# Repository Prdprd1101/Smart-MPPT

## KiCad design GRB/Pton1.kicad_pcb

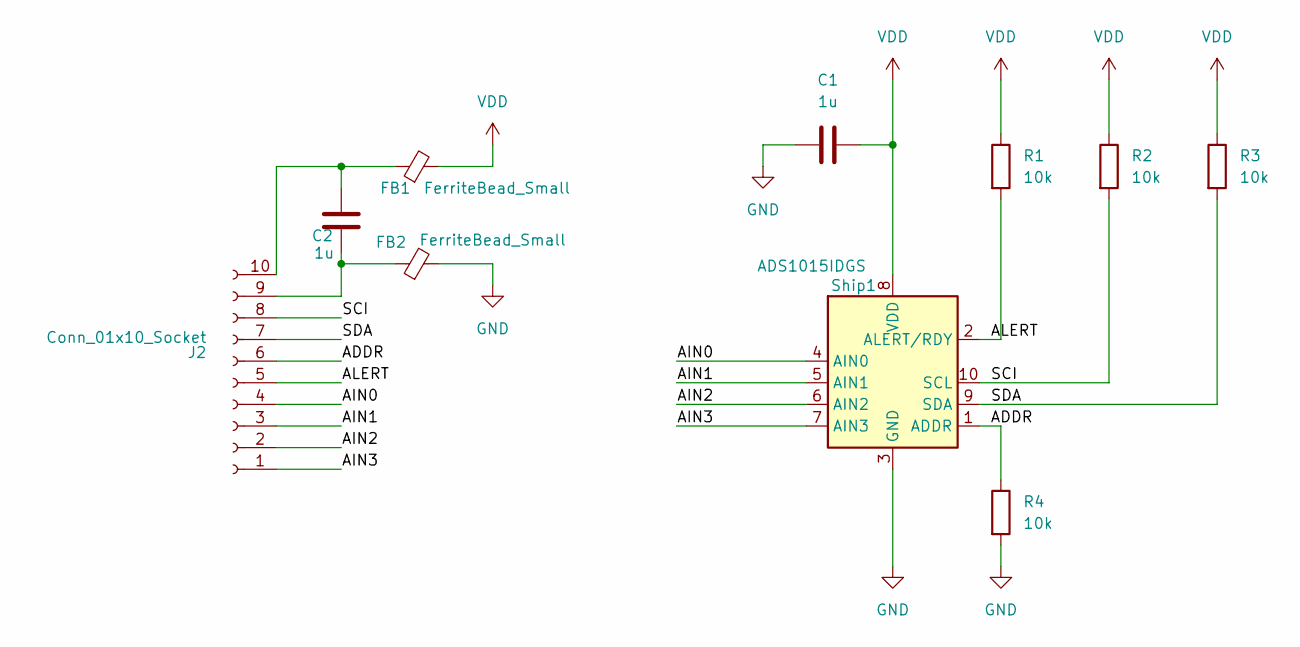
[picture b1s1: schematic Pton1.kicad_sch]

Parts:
C1, C2: 1u; CP_EIA-1608-10_AVX-L
FB1, FB2: FerriteBead_Small; L_Murata_LQH2MCNxxxx02_2.0x1.6mm
J2: Conn_01x10_Socket; PinSocket_1x10_P2.54mm_Vertical
R1, R2, R3, R4: 10k; R_0402_1005Metric
Ship1: ADS1015IDGS; TSSOP-10_3x3mm_P0.5mm

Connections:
/ADDR: J2.6, R4.1, Ship1.1 (ADDR)
/AIN0: J2.4, Ship1.4 (AIN0)
/AIN1: J2.3, Ship1.5 (AIN1)
/AIN2: J2.2, Ship1.6 (AIN2)
/AIN3: J2.1, Ship1.7 (AIN3)
/ALERT: J2.5, R1.2, Ship1.2 (ALERT/RDY)
/SCI: J2.8, R2.2, Ship1.10 (SCL)
/SDA: J2.7, R3.2, Ship1.9 (SDA)
GND: C1.1, FB2.2, R4.2, Ship1.3 (GND)
unnamed: C2.1, FB2.1, J2.9
unnamed: C2.2, FB1.1, J2.10
VDD: C1.2, FB1.2, R1.1, R2.1, R3.1, Ship1.8 (VDD)

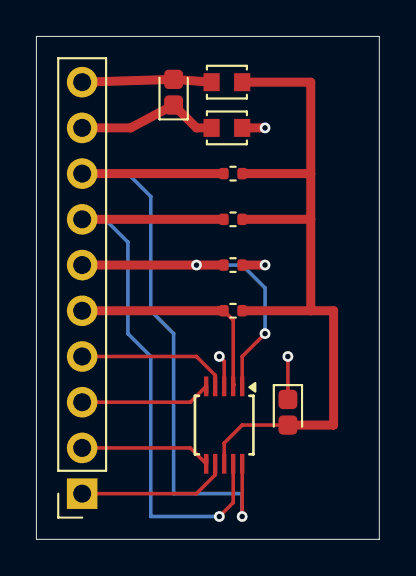
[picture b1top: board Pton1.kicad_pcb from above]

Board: 2 copper layers, 19.1 x 27.9 mm, 10 parts (0 on the bottom side), 12 nets.
